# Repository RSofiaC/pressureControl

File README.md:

# pressureControl

A pressure Control is an analog switch driven by the Vout change detected by an air pressure Sensor attached to a air input source.

## This library includes:
- [3D MODELS](https://github.com/RSofiaC/pressureControl/tree/master/3D%20Models): The 3D models used to create a costumized input
- [Arduino](https://github.com/RSofiaC/pressureControl/tree/master/Arduino): All the sketches & schematics required to drive the pressure control through an Arduino
- [ATTINY85](https://github.com/RSofiaC/pressureControl/tree/master/ATTINY85): All the sketches & schematics required to drive the pressure control through an ATTiNY85
- [Laser cutting](https://github.com/RSofiaC/pressureControl/tree/master/Laser%20cutting): Laser cutting files required to make part holders and prototypes

Refer to Arduino or ATTINY85 repos for step by step instructions

## General Specs:
- Min circuit input voltage: 4.25V
- Max circuit input voltage: 5V
- Serial communication possible
- Analog controller

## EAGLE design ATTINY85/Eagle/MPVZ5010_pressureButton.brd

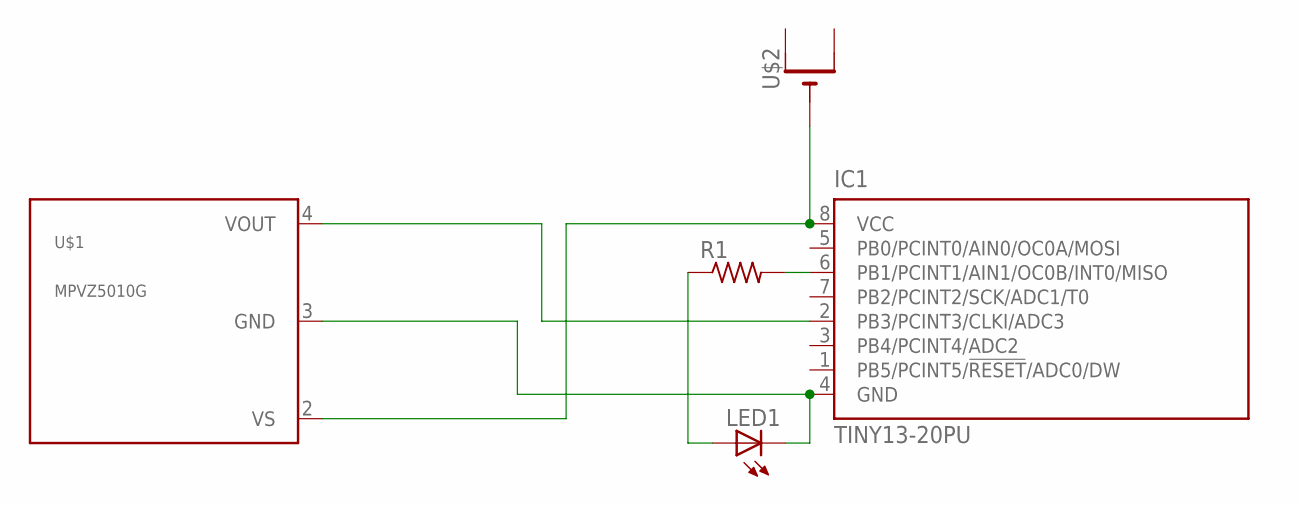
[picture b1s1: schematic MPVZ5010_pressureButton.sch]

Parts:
IC1: TINY13-20PU; DIL08
LED1: LED3MM
R1: R-US_R0805; R0805
U$1: MPVZ5010G; PVZ5010GW6U
U$2: CR1220THM; CR1220-THM

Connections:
unnamed: IC1.8 (VCC), U$1.2 (VS), U$2.-
unnamed: IC1.4 (GND), LED1.K (C), U$1.3 (GND)
unnamed: IC1.2 (PB3/PCINT3/CLKI/ADC3), U$1.4 (VOUT)
unnamed: IC1.6 (PB1/PCINT1/AIN1/OC0B/INT0/MISO), R1.2
unnamed: LED1.A, R1.1

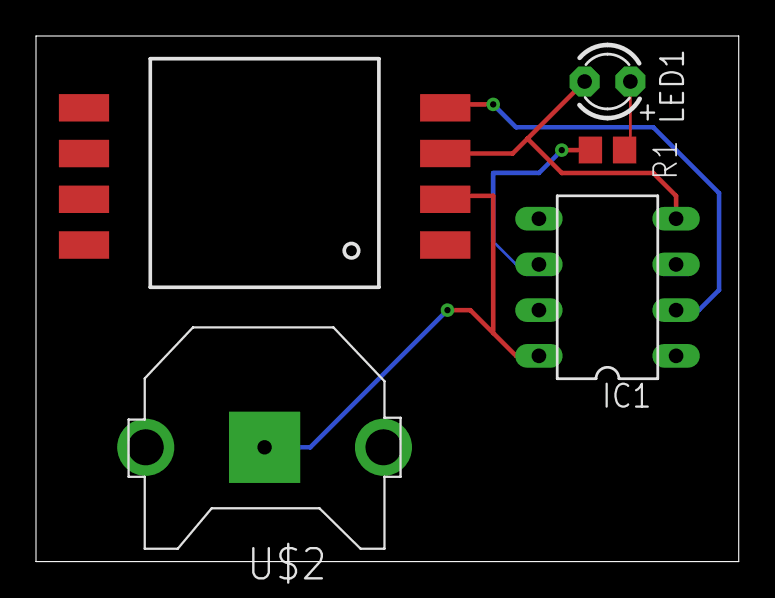
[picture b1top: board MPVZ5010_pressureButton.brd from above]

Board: 2 copper layers, 39.0 x 29.2 mm, 5 parts (0 on the bottom side), 5 nets.

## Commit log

2017-02-25 starting
2017-02-25 first try
2017-02-25 changes made in order to try and understand readings
2017-02-27 first post publication
2017-03-01 antes de irnos
2017-03-08 before final turnin
2017-10-09 Still cant make the analogwrite work, look into map value and fade control in ATTINY
2017-10-10 figured the schematic and code to use the ATTINY to control LED luminosity with MPX5010GP
2017-10-10 added schematics
2017-10-10 fritzing project
2017-10-17 updates during design with 6V cell-batteries, tried LMs -not a good idea with batteries- and improved the schematics
2017-10-19 ATTINY85 datasheet
2017-10-19 re-arranged folders for ATTINY project Arduino and General project
2017-12-01 Serial communication added to ATTiny library
2017-12-05 Create Arduino README
2017-12-05 Create ATTINY85 READ ME
2017-12-05 final update on working prototypes
2017-12-05 eagle
2017-12-14 Add files via upload
    Model created by Chester Dols
